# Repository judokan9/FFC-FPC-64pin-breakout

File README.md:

# FFC-FPC-64pin-breakout
This is just a simple FFC/FPC 64pin breakout board using the Molex 502790-6491

This could also be adapted to use one of the following connectors:
* Hirose FH52E-64S-0.5SH(99)
* KYOCERA 046288064000846+
* KYOCERA 046288064600846+

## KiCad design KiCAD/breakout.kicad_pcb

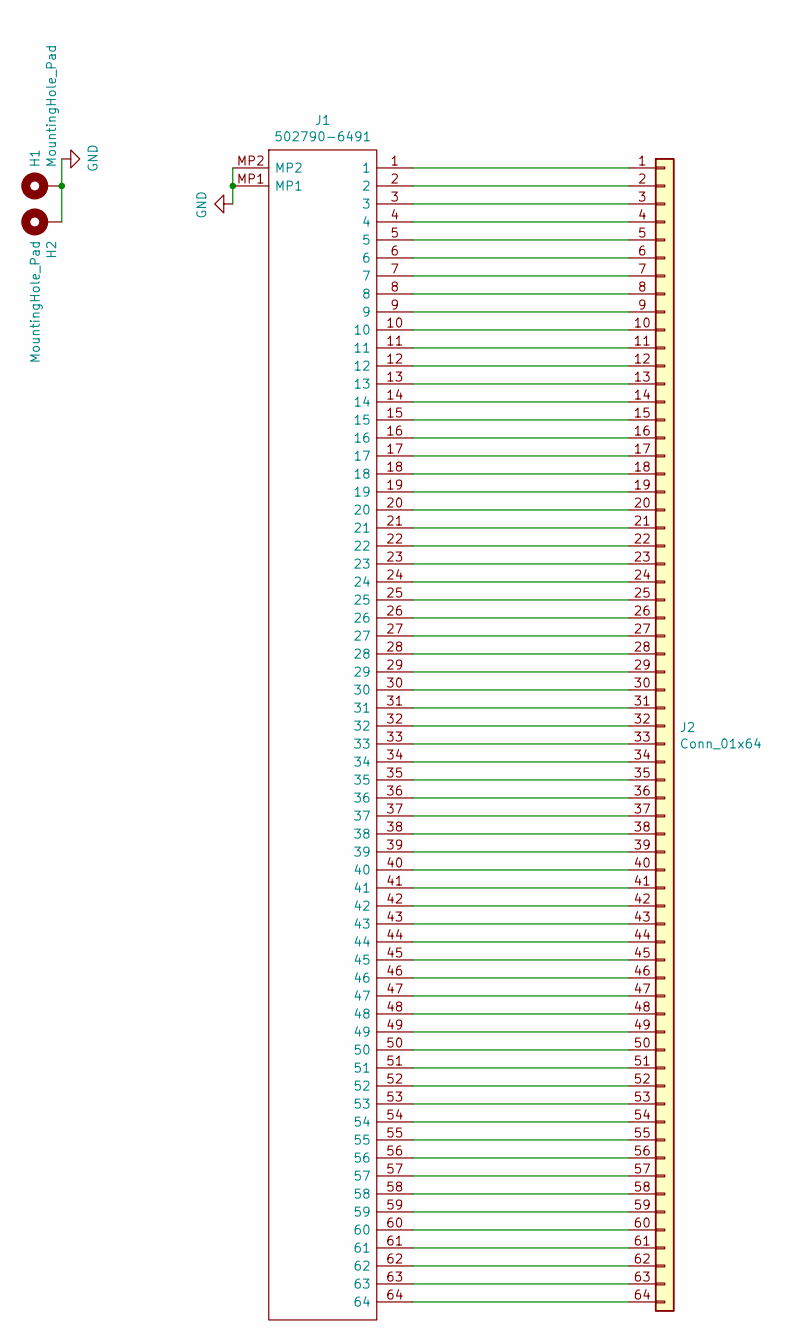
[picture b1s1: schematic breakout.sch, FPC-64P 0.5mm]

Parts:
H1, H2: MountingHole_Pad; MountingHole_3.2mm_M3_Pad_Via
J1: 502790-6491; 5027906491; Mouser Part Number 538-502790-6491
J2: Conn_01x64; PinHeader_2x32_P2.54mm_Vertical

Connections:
GND: H1.1, H2.1, J1.MP1, J1.MP2
unnamed: J1.1, J2.1
unnamed: J1.2, J2.2
unnamed: J1.3, J2.3
unnamed: J1.4, J2.4
unnamed: J1.5, J2.5
unnamed: J1.6, J2.6
unnamed: J1.7, J2.7
unnamed: J1.8, J2.8
unnamed: J1.9, J2.9
unnamed: J1.10, J2.10
unnamed: J1.11, J2.11
unnamed: J1.12, J2.12
unnamed: J1.13, J2.13
unnamed: J1.14, J2.14
unnamed: J1.15, J2.15
unnamed: J1.16, J2.16
unnamed: J1.17, J2.17
unnamed: J1.18, J2.18
unnamed: J1.19, J2.19
unnamed: J1.20, J2.20
unnamed: J1.21, J2.21
unnamed: J1.22, J2.22
unnamed: J1.23, J2.23
unnamed: J1.24, J2.24
unnamed: J1.25, J2.25
unnamed: J1.26, J2.26
unnamed: J1.27, J2.27
unnamed: J1.28, J2.28
unnamed: J1.29, J2.29
unnamed: J1.30, J2.30
unnamed: J1.31, J2.31
unnamed: J1.32, J2.32
unnamed: J1.33, J2.33
unnamed: J1.34, J2.34
unnamed: J1.35, J2.35
unnamed: J1.36, J2.36
unnamed: J1.37, J2.37
unnamed: J1.38, J2.38
unnamed: J1.39, J2.39
unnamed: J1.40, J2.40
unnamed: J1.41, J2.41
unnamed: J1.42, J2.42
unnamed: J1.43, J2.43
unnamed: J1.44, J2.44
unnamed: J1.45, J2.45
unnamed: J1.46, J2.46
unnamed: J1.47, J2.47
unnamed: J1.48, J2.48
unnamed: J1.49, J2.49
unnamed: J1.50, J2.50
unnamed: J1.51, J2.51
unnamed: J1.52, J2.52
unnamed: J1.53, J2.53
unnamed: J1.54, J2.54
unnamed: J1.55, J2.55
unnamed: J1.56, J2.56
unnamed: J1.57, J2.57
unnamed: J1.58, J2.58
unnamed: J1.59, J2.59
unnamed: J1.60, J2.60
unnamed: J1.61, J2.61
unnamed: J1.62, J2.62
unnamed: J1.63, J2.63
unnamed: J1.64, J2.64

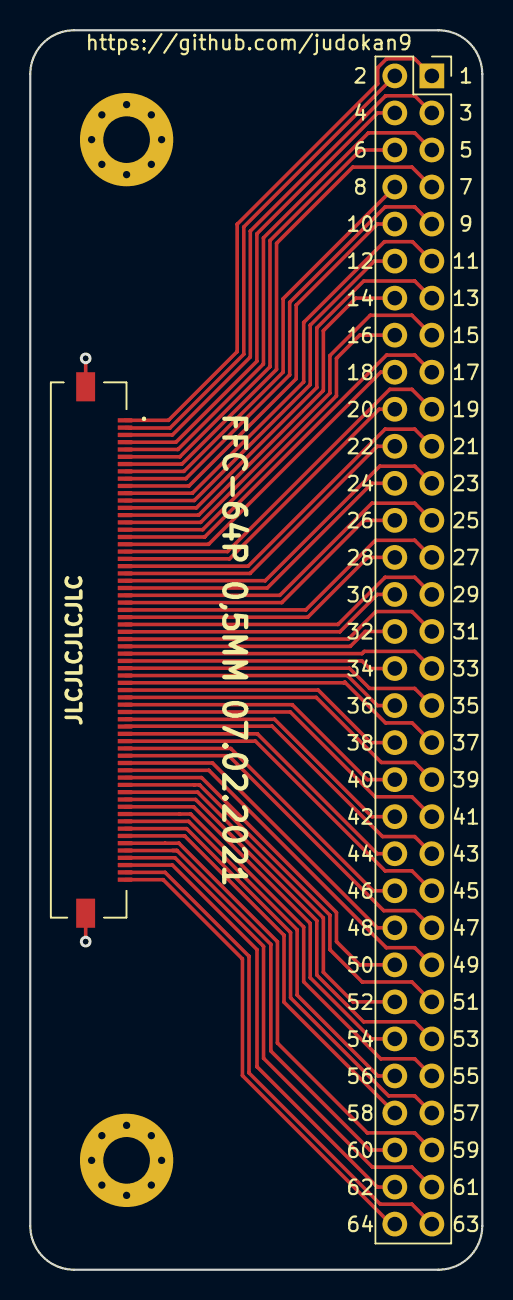
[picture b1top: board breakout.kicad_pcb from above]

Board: 2 copper layers, 31.0 x 85.0 mm, 4 parts (0 on the bottom side), 65 nets.

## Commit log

2021-02-09 Update README.md
    Added connectors
2021-02-09 Added board files
2021-02-09 Update README.md
    added pictures
2021-02-09 added pictures
2021-02-09 Update README.md
    changed image size
2021-02-09 Update README.md
    added list
